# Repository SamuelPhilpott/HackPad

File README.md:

# HackPad
Half my time working on my own stuff is me switching tabs and adjusting settings back (Yes I use a family computer), Because of this My effitency is limited so following hack clubs wonderfull tutorial I made my own macropad!

assembled:

Its just a sandwich of boards held together withs screws

PCB:

Scmatics: 

BOM

XIAO X1
1x EC11 Rotary Encoder
x2 WS2812B LEDs
4x Cherry MX Switches
x4 Heated inserts
x3 5x M3x5x4 Heatset inserts

#Notes

Sorry about the poor quality, my computer is freaking out i dont know why Its never fully worked and so ive tryed my best (i cant afford a new computer but working to it!)

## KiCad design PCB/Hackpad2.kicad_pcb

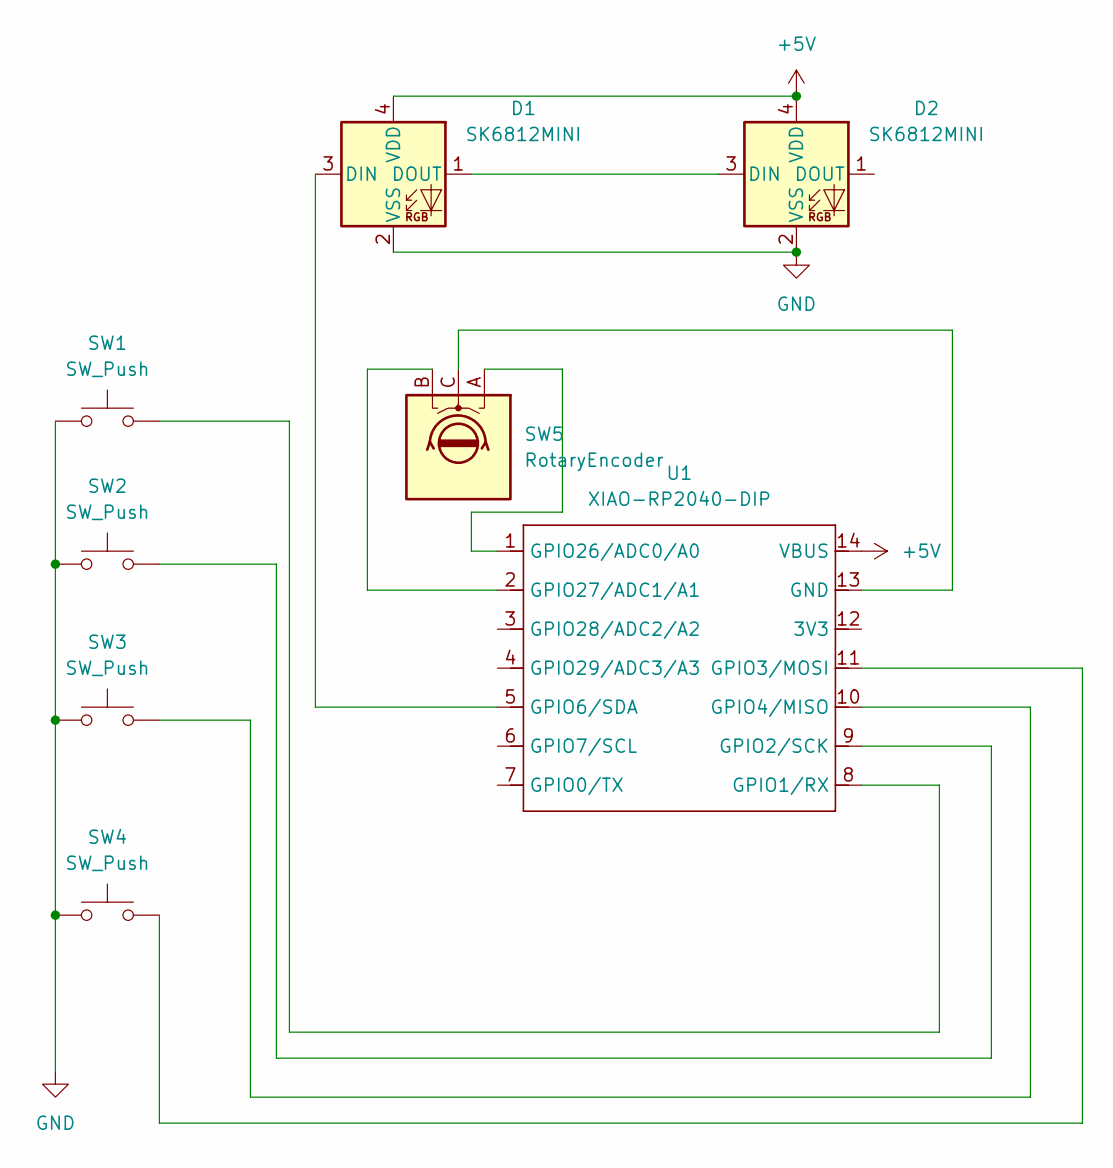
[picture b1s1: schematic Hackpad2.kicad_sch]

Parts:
D1, D2: SK6812MINI; LED_SK6812MINI_PLCC4_3.5x3.5mm_P1.75mm
SW1, SW2, SW3, SW4: SW_Push; SW_Cherry_MX_1.00u_PCB
SW5: RotaryEncoder; RotaryEncoder_Alps_EC11E_Vertical_H20mm
U1: XIAO-RP2040-DIP

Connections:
+5V: D1.4 (VDD), D2.4 (VDD), U1.14 (VBUS)
GND: D1.2 (VSS), D2.2 (VSS), SW1.1, SW2.1, SW3.1, SW4.1
unnamed: D1.3 (DIN), U1.5 (GPIO6/SDA)
unnamed: D1.1 (DOUT), D2.3 (DIN)
unnamed: SW5.C, U1.13 (GND)
unnamed: SW1.2, U1.8 (GPIO1/RX)
unnamed: SW2.2, U1.9 (GPIO2/SCK)
unnamed: SW4.2, U1.11 (GPIO3/MOSI)
unnamed: SW3.2, U1.10 (GPIO4/MISO)
unnamed: SW5.A, U1.1 (GPIO26/ADC0/A0)
unnamed: SW5.B, U1.2 (GPIO27/ADC1/A1)

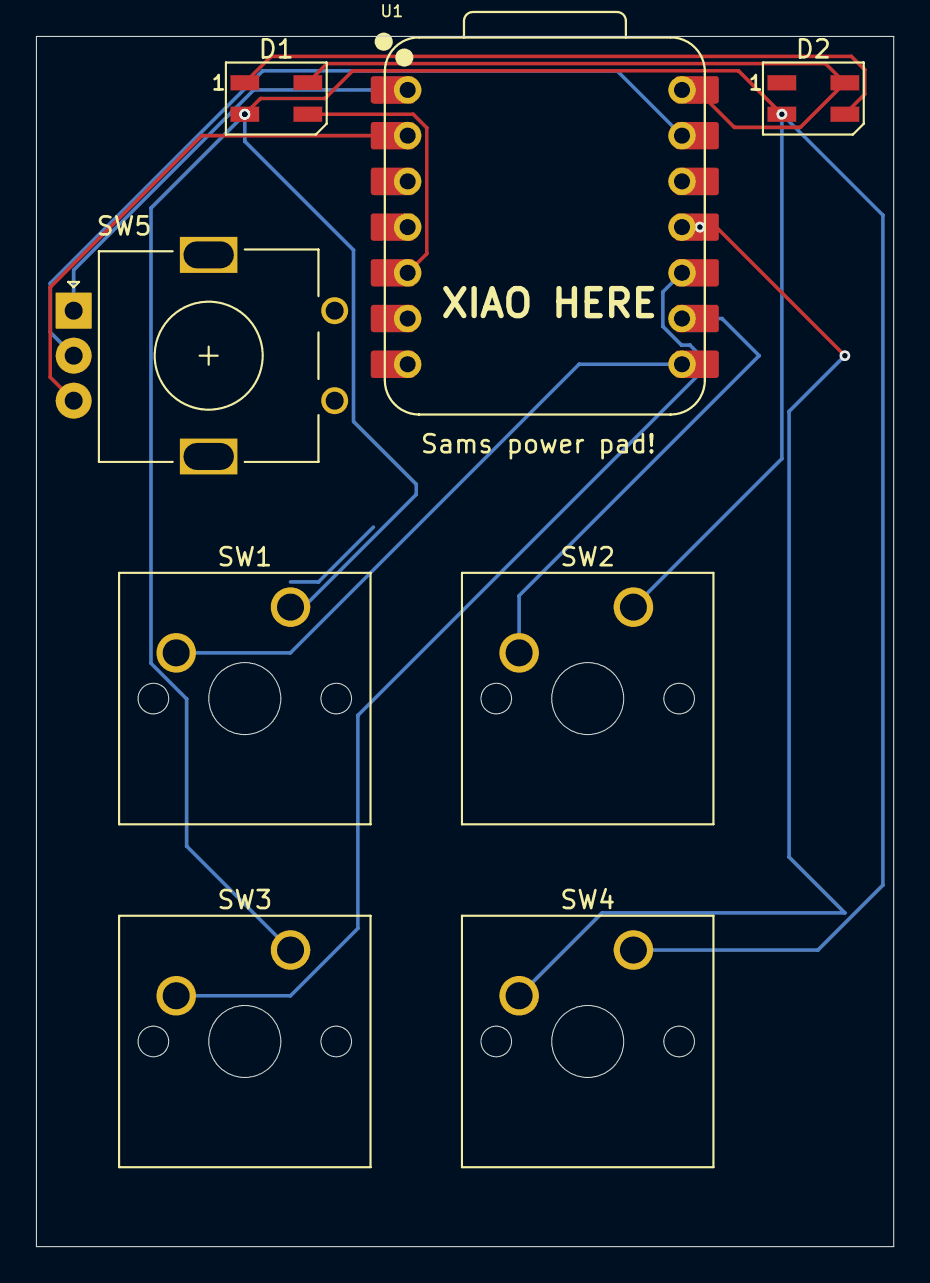
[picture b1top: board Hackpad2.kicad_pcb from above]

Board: 2 copper layers, 47.6 x 67.2 mm, 8 parts (0 on the bottom side), 11 nets.

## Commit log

2025-11-25 Create PCB
2025-11-25 Create CAD
2025-11-25 Create Code
2025-11-25 Update README with BOM and notes
    Added Bill of Materials (BOM) and notes section to README.
2025-11-26 Add Hack Pad Case CAD file
2025-12-04 New code that works
